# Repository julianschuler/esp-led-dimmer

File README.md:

# ESP LED Dimmer

*Four dimmers shown in different configurations from left to right: Fully assembled within a case, fully assembled, without the ESP-01 module and from the back.*

## Overview

This repository contains the PCB files for a wireless dimmer for up to two monochromatic LED strips based on the ESP-01. It can e.g. be integrated into [Home Assistant](https://www.home-assistant.io/) using [ESPHome](https://esphome.io/).

The dimmer is powered via a DC barrel jack and supports both 12V and 24V LED strips. The LED strips are connected via screw terminals.

It is designed to make use of the PCBA services of JLCPCB and uses as many basic parts as possible. You can use the awesome [KiCAD JLCPCB tools](https://github.com/Bouni/kicad-jlcpcb-tools) for exporting the corresponding fabrication files.
Excluding the ESP-01 module, the cost per assembled PCB is around 5€.

> **Warning:** Only power up the dimmer when the ESP-01 module is plugged in, otherwise it might get broken! This seems to be due to the power supply IC requiring a certain minimum current to be drawn.

## Using the dimmer with Home Assistant

To use the dimmer with Home Assistant, create a new ESP8266 device in the [ESPHome Device Builder](https://esphome.io/guides/getting_started_hassio.html) and append the following lines to its YAML file:

```yaml
output:
  - id: led1
    pin: GPIO2
    platform: esp8266_pwm
    frequency: 1000 Hz
  - id: led2
    pin: GPIO0
    platform: esp8266_pwm
    frequency: 1000 Hz

light:
  - output: led1
    name: "LED 1"
    platform: monochromatic
  - output: led2
    name: "LED 2"
    platform: monochromatic
```

Install the resulting configuration to the ESP-01 and insert it into the corresponding header on the dimmer.
Within a minute the dimmer should be available within Home Assistant.

## License

This project is licensed under the MIT license, see [`LICENSE.txt`](LICENSE.txt) for further information.

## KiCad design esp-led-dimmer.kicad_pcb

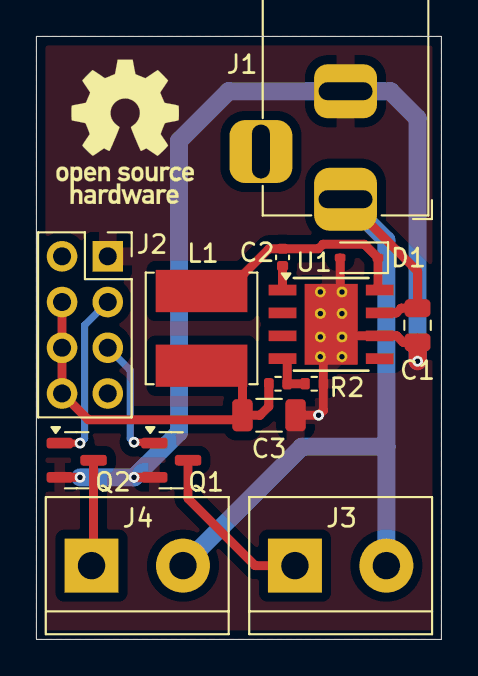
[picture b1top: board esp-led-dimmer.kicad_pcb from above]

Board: 2 copper layers, 22.5 x 33.5 mm, 14 parts (0 on the bottom side), 10 nets.

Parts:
C1: 4.7µF; C_0805_2012Metric
C2: 10nF; C_0402_1005Metric
C3: 100µF; C_1206_3216Metric
D1: 1N5819; D_SOD-323
J1: Barrel Jack 3A; BarrelJack_Horizontal
J2: ESP-01; PinSocket_2x04_P2.54mm_Vertical
J3: LED 1; TerminalBlock_bornier-2_P5.08mm
J4: LED 2; TerminalBlock_bornier-2_P5.08mm
L1: 100µH; L_Bourns_SRN6045TA
Q1, Q2: AO3400A; SOT-23
R1: 10kΩ; R_0402_1005Metric
R2: 5.9kΩ; R_0402_1005Metric
U1: TPS5430DDA; TI_SO-PowerPAD-8_ThermalVias

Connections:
+3.3V: C3.2, J2.4, J2.6, J2.8, L1.1, R1.1
+24V: C1.2, J1.1, J3.2, J4.2, U1.7 (VIN)
GND: C1.1, C3.1, D1.2 (A), J1.2, J2.1, Q1.2 (S), Q2.2 (S), R2.2, U1.6 (GND), U1.9 (GNDPAD)
LED1: J2.5, Q1.1 (G)
LED2: J2.3, Q2.1 (G)
unnamed: C2.2, D1.1 (K), L1.2, U1.8 (PH)
unnamed: J3.1, Q1.3 (D)
unnamed: J4.1, Q2.3 (D)
unnamed: C2.1, U1.1 (BOOT)
VSENSE: R1.2, R2.1, U1.4 (VSENSE)

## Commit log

2025-02-04 Add license
2025-02-04 Add .gitignore
2025-02-04 Add basic power supply circuit
2025-02-04 Add LED dimming circuit
2025-02-04 Replace LM2564 with TPS5430 for 3.3V power supply
2025-02-06 Assign footprints to schematic symbols
2025-02-06 Add PCB design
2025-02-07 Add JLCPCB component IDs for PCBA
2025-02-07 Adjust pin placement for barrel jack
2025-02-07 Remove JLCPCB order marker placeholder
2025-02-07 Replace screw terminal footprints
2025-02-18 Move pcb files to subfolder
2025-02-18 Add README.md
2025-02-24 Add case
2025-02-28 Describe how to use the dimmer with Home Assistant
2025-03-03 Add a warning not to use the dimmer without ESP-01
2025-03-03 Add image of dimmers in different configurations
